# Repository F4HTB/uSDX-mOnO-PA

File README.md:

# uSDX-mOnO-PA
Power Amplifier for uSDX Mono.  

This is a alpha version of 10m power amplifier for uSDX mOnO.  
It will take place in the last layer of the uSDX mOnO.  

Note that it is currently in testing.  
I keep making things better.  
Currently ~10w @ 28mhz with harmonics below 46dbc.  

The simulation folder contains an LTspice equivalent.  

Please read the notes in the diagram.

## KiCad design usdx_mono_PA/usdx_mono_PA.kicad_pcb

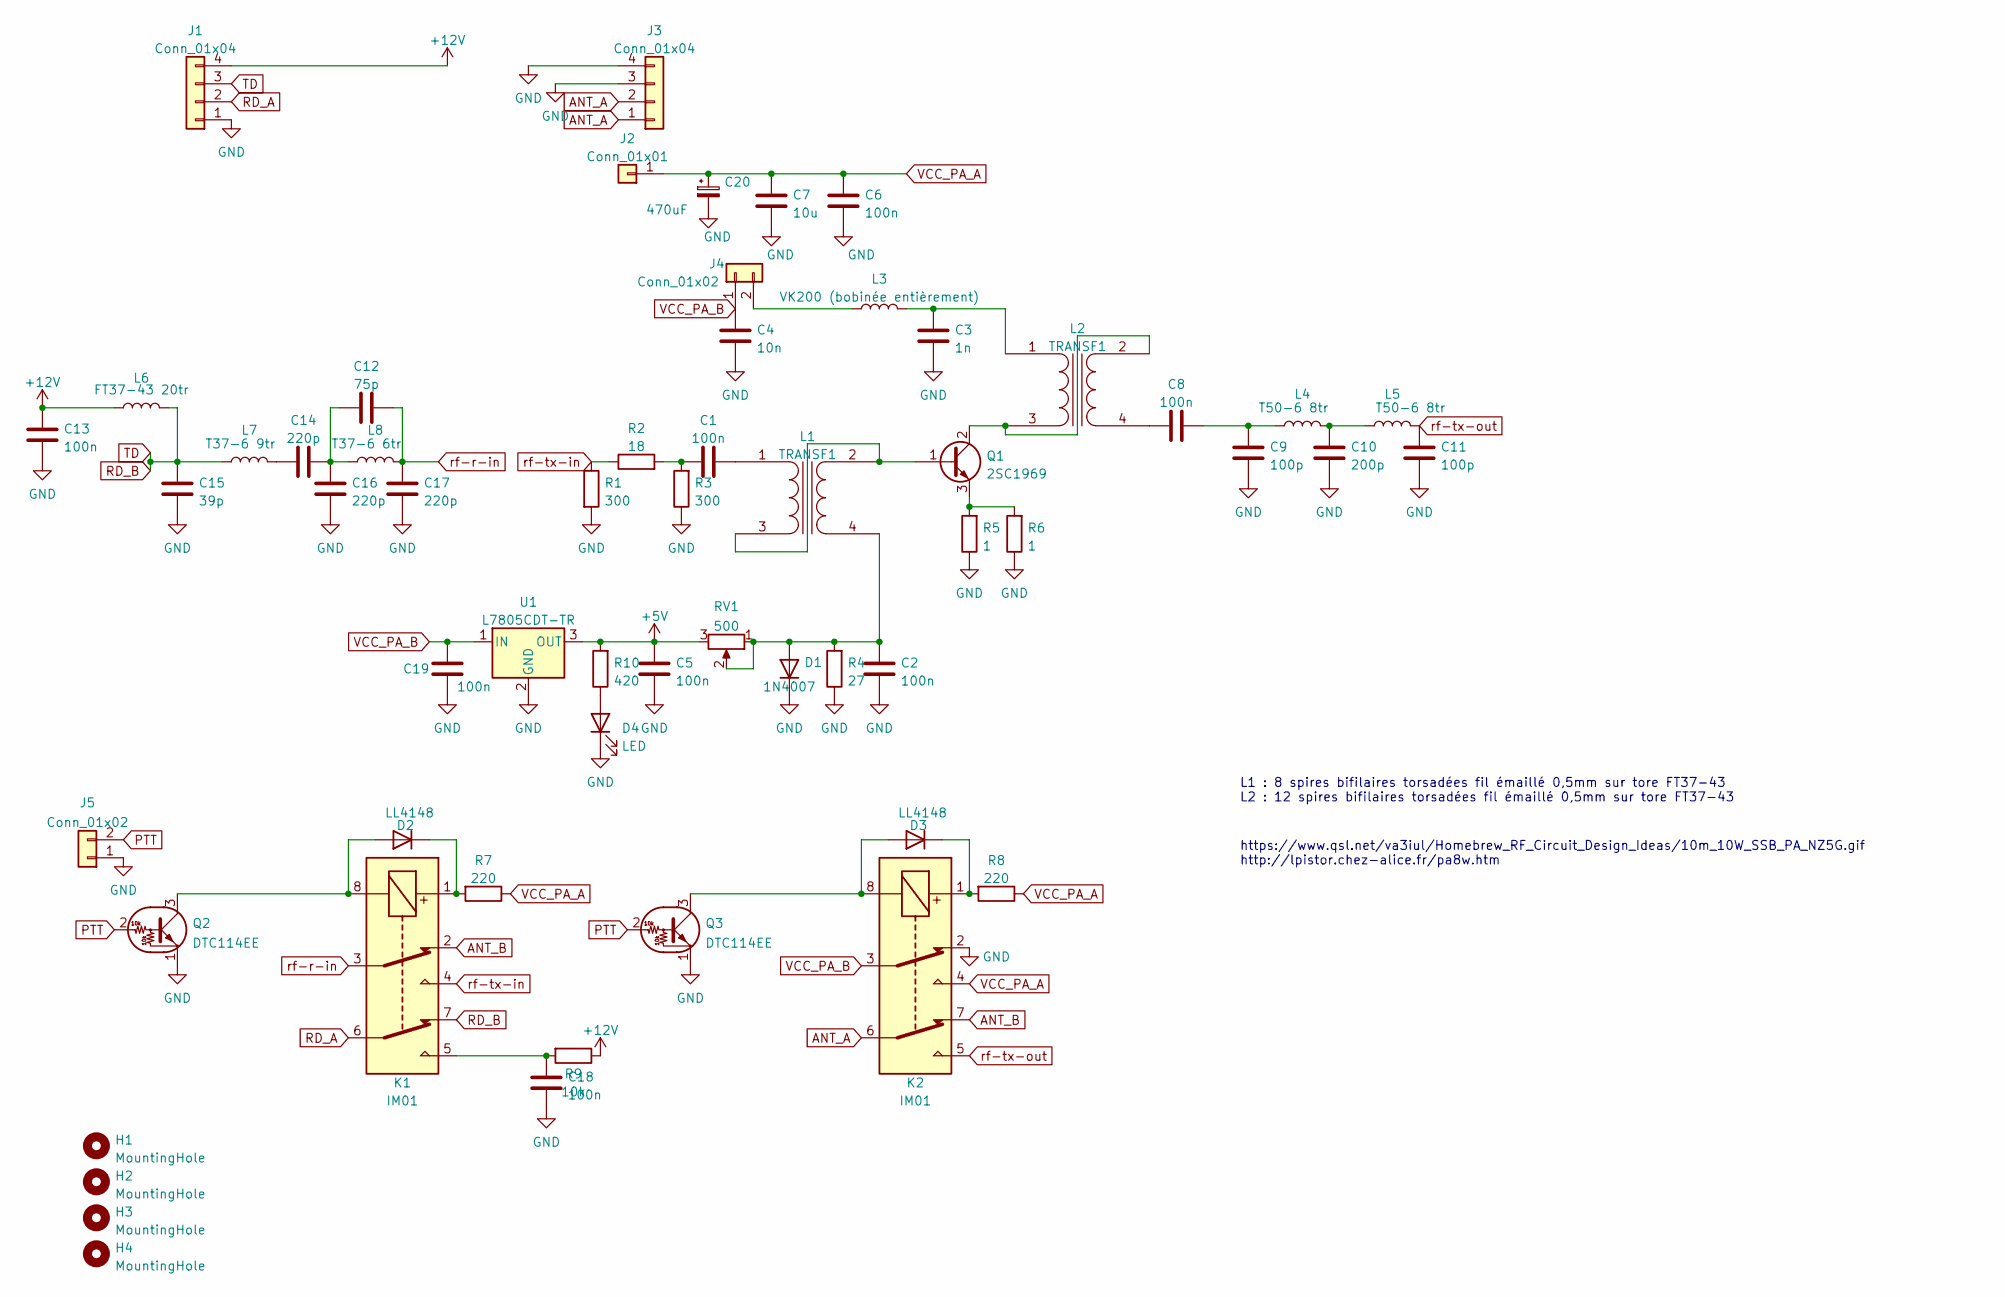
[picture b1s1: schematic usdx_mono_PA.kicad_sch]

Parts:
C1, C2, C5, C8, C13, C18, C19: 100n; C_0805_2012Metric_Pad1.18x1.45mm_HandSolder
C3: 1n; C_0805_2012Metric_Pad1.18x1.45mm_HandSolder
C4: 10n; C_0805_2012Metric_Pad1.18x1.45mm_HandSolder
C6: 100n; C_0402_1005Metric
C7: 10u; C_1210_3225Metric_Pad1.33x2.70mm_HandSolder
C9, C11: 100p; C_0805_2012Metric_Pad1.18x1.45mm_HandSolder
C10: 200p; C_0805_2012Metric_Pad1.18x1.45mm_HandSolder
C12: 75p; C_0805_2012Metric_Pad1.18x1.45mm_HandSolder
C14, C16, C17: 220p; C_0805_2012Metric_Pad1.18x1.45mm_HandSolder
C15: 39p; C_0805_2012Metric_Pad1.18x1.45mm_HandSolder
C20: 470uF; C_0805_2012Metric_Pad1.18x1.45mm_HandSolder
D1: 1N4007; D_MiniMELF_Handsoldering
D2, D3: LL4148; D_MiniMELF
D4: LED; LED_0805_2012Metric_Pad1.15x1.40mm_HandSolder
H1, H2, H3, H4: MountingHole; MountingHole_3.2mm_M3_ISO14580
J1, J3: Conn_01x04; PinHeader_1x04_P2.54mm_Vertical
J2: Conn_01x01; PinHeader_1x01_P2.54mm_Vertical
J4: Conn_01x02; SolderJumper-2_P1.3mm_Open_RoundedPad1.0x1.5mm
J5: Conn_01x02; PinHeader_1x02_P1.27mm_Vertical
K1, K2: IM01; Relay_DPDT_AXICOM_IMSeries_JLeg
L1, L2: TRANSF1; PinHeader_1x04_P2.54mm_Vertical
L3: VK200 (bobinée entièrement); L_Radial_D6.0mm_P4.00mm
L4, L5: T50-6 8tr; FT37-XX
L6: FT37-43 20tr; FT37-XX
L7: T37-6 9tr; FT37-XX
L8: T37-6 6tr; FT37-XX
Q1: 2SC1969; TO-220-3_Horizontal_TabDown
Q2, Q3: DTC114EE
R1, R3: 300; R_2512_6332Metric_Pad1.40x3.35mm_HandSolder
R2: 18; R_2512_6332Metric_Pad1.40x3.35mm_HandSolder
R4: 27; R_0805_2012Metric_Pad1.20x1.40mm_HandSolder
R5, R6: 1; R_0805_2012Metric_Pad1.20x1.40mm_HandSolder
R7, R8: 220; R_0805_2012Metric_Pad1.20x1.40mm_HandSolder
R9: 10k; R_0805_2012Metric_Pad1.20x1.40mm_HandSolder
R10: 420; R_0805_2012Metric_Pad1.20x1.40mm_HandSolder
RV1: 500; PinHeader_1x03_P2.54mm_Vertical
U1: L7805CDT-TR; TO-252-2

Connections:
+5V: C5.2, R10.2, RV1.3, U1.3 (OUT)
+12V: C13.2, J1.4, L6.1, R9.1
ANT_A: J3.1, J3.2, K2.6
ANT_B: K1.2, K2.7
GND: C2.1, C3.1, C4.1, C5.1, C6.1, C7.1, C9.2, C10.2, C11.2, C13.1, C15.1, C16.1, C17.1, C18.1, C19.1, C20.2, D1.1 (K), D4.1 (K), J1.1, J3.3, J3.4, J5.1, K2.2, Q2.1 (E), Q3.1 (E), R1.2, R3.1, R4.1, R5.1, R6.1, U1.2 (GND)
unnamed: C1.1, R2.2, R3.2
unnamed: C1.2, L1.1
unnamed: C2.2, D1.2 (A), L1.4, R4.2, RV1.1, RV1.2
unnamed: C3.2, L2.1, L3.2
unnamed: C8.1, C9.1, L4.1
unnamed: C8.2, L2.4
unnamed: C10.1, L4.2, L5.1
unnamed: C12.2, C14.1, C16.2, L8.1
unnamed: C14.2, L7.2
unnamed: C18.2, K1.5, R9.2
unnamed: D2.1 (K), K1.1, R7.2
unnamed: D2.2 (A), K1.8, Q2.3 (C)
unnamed: D3.1 (K), K2.1, R8.2
unnamed: D3.2 (A), K2.8, Q3.3 (C)
unnamed: D4.2 (A), R10.1
unnamed: J4.2, L3.1
unnamed: L1.2, L1.3, Q1.1 (B)
unnamed: L2.2, L2.3, Q1.2 (C)
unnamed: Q1.3 (E), R5.2, R6.2
PTT: J5.2, Q2.2 (B), Q3.2 (B)
RD_A: J1.2, K1.6
RD_B: C15.2, J1.3, K1.7, L6.2, L7.1
VCC_PA_A: C6.2, C7.2, C20.1, J2.1, K2.4, R7.1, R8.1
VCC_PA_B: C4.2, C19.2, J4.1, K2.3, U1.1 (IN)
rf-r-in: C12.1, C17.2, K1.3, L8.2
rf-tx-in: K1.4, R1.1, R2.1
rf-tx-out: C11.1, K2.5, L5.2

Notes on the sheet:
L1 : 8 spires bifilaires torsadées fil émaillé 0,5mm sur tore FT37-43 L2 : 12 spires bifilaires torsadées fil émaillé 0,5mm sur tore FT37-43
https://www.qsl.net/va3iul/Homebrew_RF_Circuit_Design_Ideas/10m_10W_SSB_PA_NZ5G.gif http://lpistor.chez-alice.fr/pa8w.htm

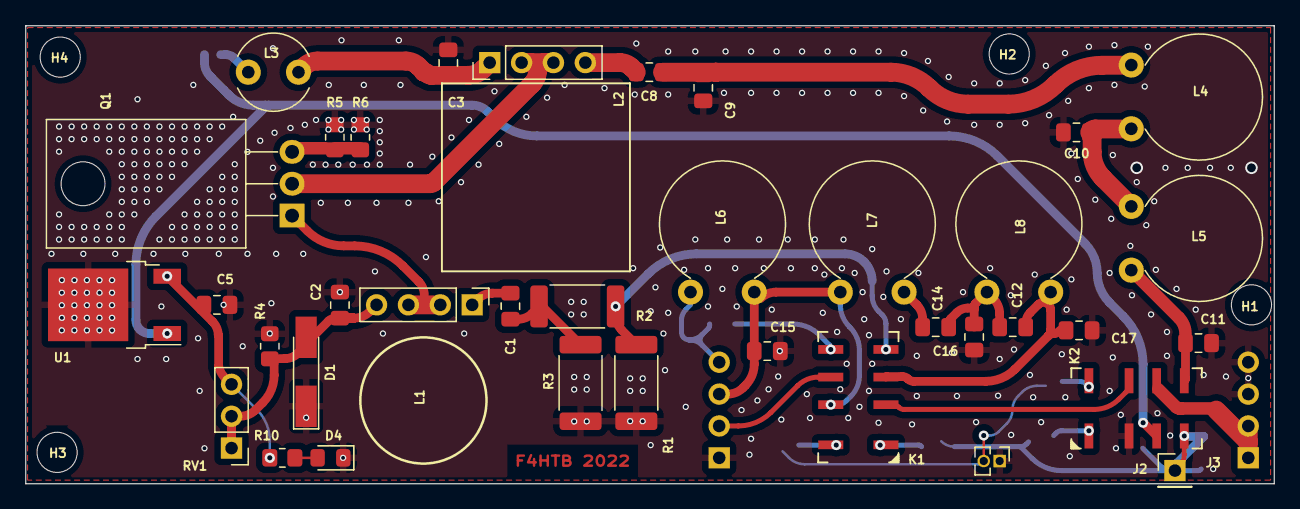
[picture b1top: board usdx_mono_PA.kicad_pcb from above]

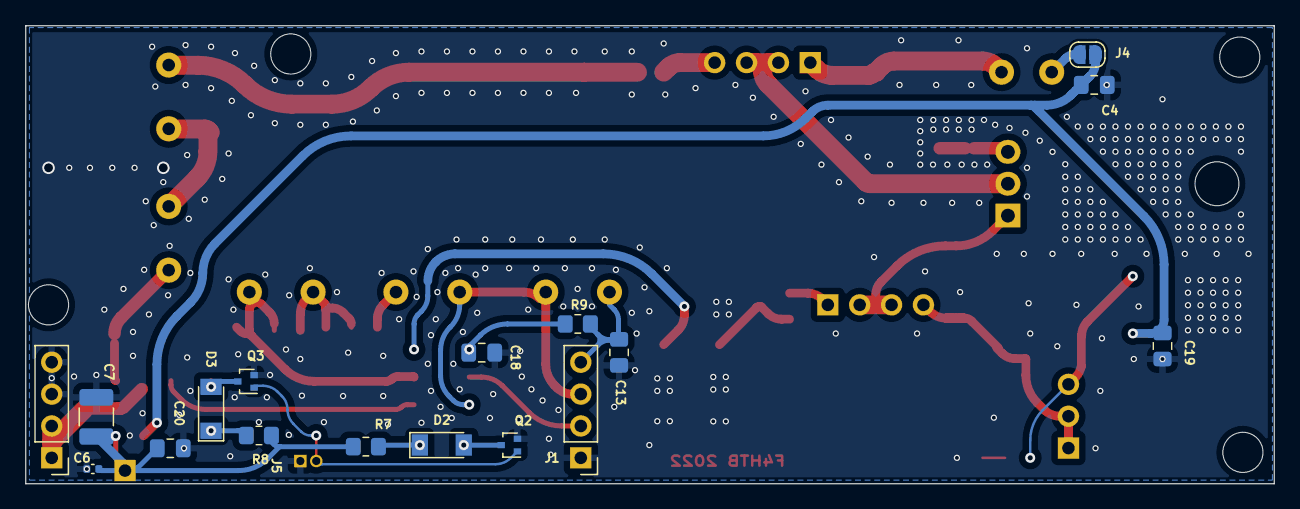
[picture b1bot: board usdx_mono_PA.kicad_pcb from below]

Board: 2 copper layers, 99.5 x 36.5 mm, 58 parts (17 on the bottom side), 32 nets.

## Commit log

2022-03-11 add images
2022-03-11 add mods
2022-03-11 add mods on pcb
2022-04-07 add mods and simulation files
2022-04-08 add measures and eliptic low pass filter modifications
2022-04-08 readme mods
